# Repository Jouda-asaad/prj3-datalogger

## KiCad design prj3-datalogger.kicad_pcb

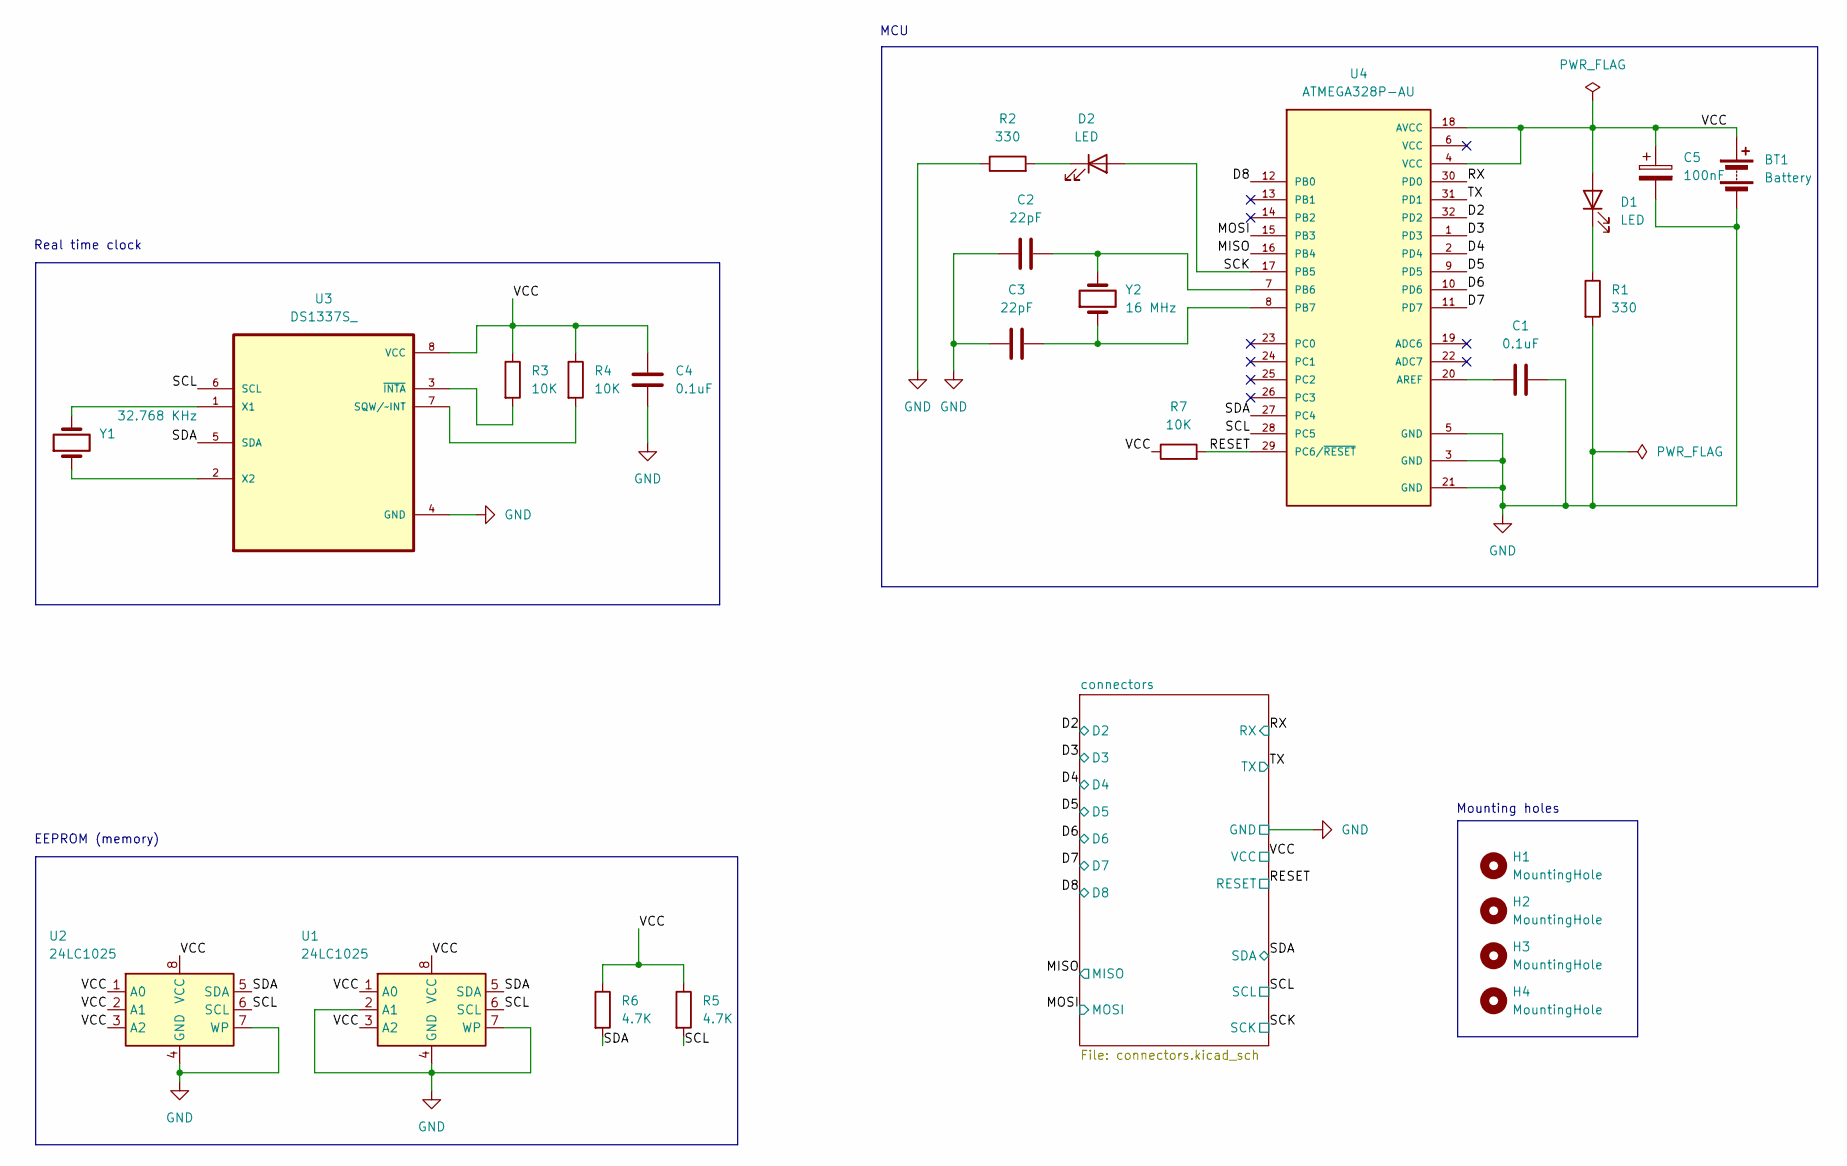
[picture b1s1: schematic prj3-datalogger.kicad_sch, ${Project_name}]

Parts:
BT1: Battery; PinHeader_1x02_P2.54mm_Vertical
C1, C4: 0.1uF; C_0805_2012Metric
C2, C3: 22pF; C_0805_2012Metric
C5: 100nF; C_0805_2012Metric
D1, D2: LED; LED_0805_2012Metric
H1, H2, H3, H4: MountingHole; MountingHole_2.2mm_M2
R1, R2: 330; R_0805_2012Metric
R3, R4, R7: 10K; R_0805_2012Metric
R5, R6: 4.7K; R_0805_2012Metric
U1, U2: 24LC1025; SOIC-8_5.3x5.3mm_P1.27mm
U3: DS1337S_; SOIC127P600X175-8N
U4: ATMEGA328P-AU; QFP80P900X900X120-32N; PARTREV 8271A
Y1: 32.768 KHz; Crystal_SMD_5032-2Pin_5.0x3.2mm_HandSoldering
Y2: 16 MHz; Crystal_SMD_5032-2Pin_5.0x3.2mm_HandSoldering

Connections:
/D2: U4.32 (PD2); also elsewhere on the board
/D3: U4.1 (PD3); also elsewhere on the board
/D4: U4.2 (PD4); also elsewhere on the board
/D5: U4.9 (PD5); also elsewhere on the board
/D6: U4.10 (PD6); also elsewhere on the board
/D7: U4.11 (PD7); also elsewhere on the board
/D8: U4.12 (PB0); also elsewhere on the board
/MISO: U4.16 (PB4); also elsewhere on the board
/MOSI: U4.15 (PB3); also elsewhere on the board
/RESET: R7.2, U4.29 (PC6/~RESET); also elsewhere on the board
/RX: U4.30 (PD0); also elsewhere on the board
/SCK: D2.2 (A), U4.17 (PB5); also elsewhere on the board
/SCL: R5.2, U1.6 (SCL), U2.6 (SCL), U3.6 (SCL), U4.28 (PC5); also elsewhere on the board
/SDA: R6.2, U1.5 (SDA), U2.5 (SDA), U3.5 (SDA), U4.27 (PC4); also elsewhere on the board
/TX: U4.31 (PD1); also elsewhere on the board
/VCC: BT1.1 (+), C4.1, C5.1, D1.2 (A), R3.1, R4.1, R5.1, R6.1, R7.1, U1.1 (A0), U1.3 (A2), U1.8 (VCC), U2.1 (A0), U2.2 (A1), U2.3 (A2), U2.8 (VCC), U3.8 (VCC), U4.4 (VCC), U4.18 (AVCC); also elsewhere on the board
GND: BT1.2 (-), C1.2, C2.1, C3.1, C4.2, C5.2, R1.2, R2.1, U1.2 (A1), U1.4 (GND), U1.7 (WP), U2.4 (GND), U2.7 (WP), U3.4 (GND), U4.3 (GND), U4.5 (GND), U4.21 (GND); also elsewhere on the board
unnamed: D1.1 (K), R1.1
unnamed: D2.1 (K), R2.2
unnamed: R4.2, U3.7 (SQW/~INT)
unnamed: U3.1 (X1), Y1.2
unnamed: U3.2 (X2), Y1.1
unnamed: R3.2, U3.3 (~INTA)
unnamed: C1.1, U4.20 (AREF)
unnamed: C2.2, U4.7 (PB6), Y2.2
unnamed: C3.2, U4.8 (PB7), Y2.1

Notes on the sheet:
EEPROM (memory)
MCU
Mounting holes
Real time clock

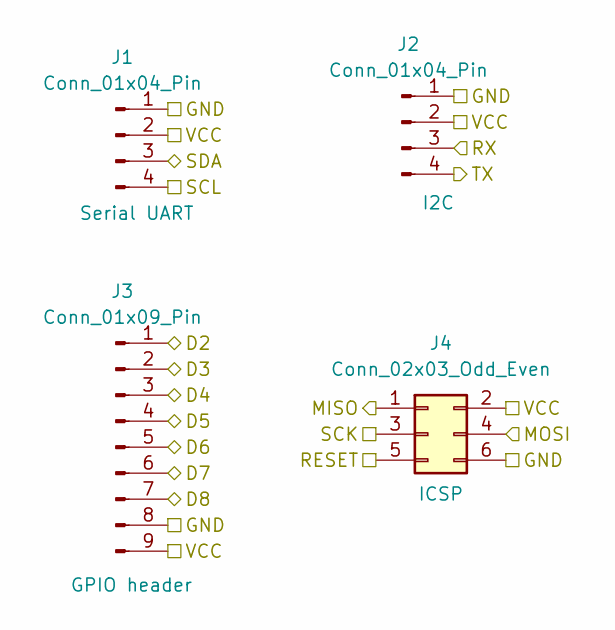
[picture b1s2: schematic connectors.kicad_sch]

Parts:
J1, J2: Conn_01x04_Pin; PinHeader_1x04_P2.54mm_Vertical
J3: Conn_01x09_Pin; PinHeader_1x10_P2.54mm_Vertical
J4: Conn_02x03_Odd_Even; PinHeader_2x03_P2.54mm_Vertical

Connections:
/D2: J3.1; also elsewhere on the board
/D3: J3.2; also elsewhere on the board
/D4: J3.3; also elsewhere on the board
/D5: J3.4; also elsewhere on the board
/D6: J3.5; also elsewhere on the board
/D7: J3.6; also elsewhere on the board
/D8: J3.7; also elsewhere on the board
/MISO: J4.1; also elsewhere on the board
/MOSI: J4.4; also elsewhere on the board
/RESET: J4.5; also elsewhere on the board
/RX: J2.3; also elsewhere on the board
/SCK: J4.3; also elsewhere on the board
/SCL: J1.4; also elsewhere on the board
/SDA: J1.3; also elsewhere on the board
/TX: J2.4; also elsewhere on the board
/VCC: J1.2, J2.2, J3.9, J4.2; also elsewhere on the board
GND: J1.1, J2.1, J3.8, J4.6; also elsewhere on the board

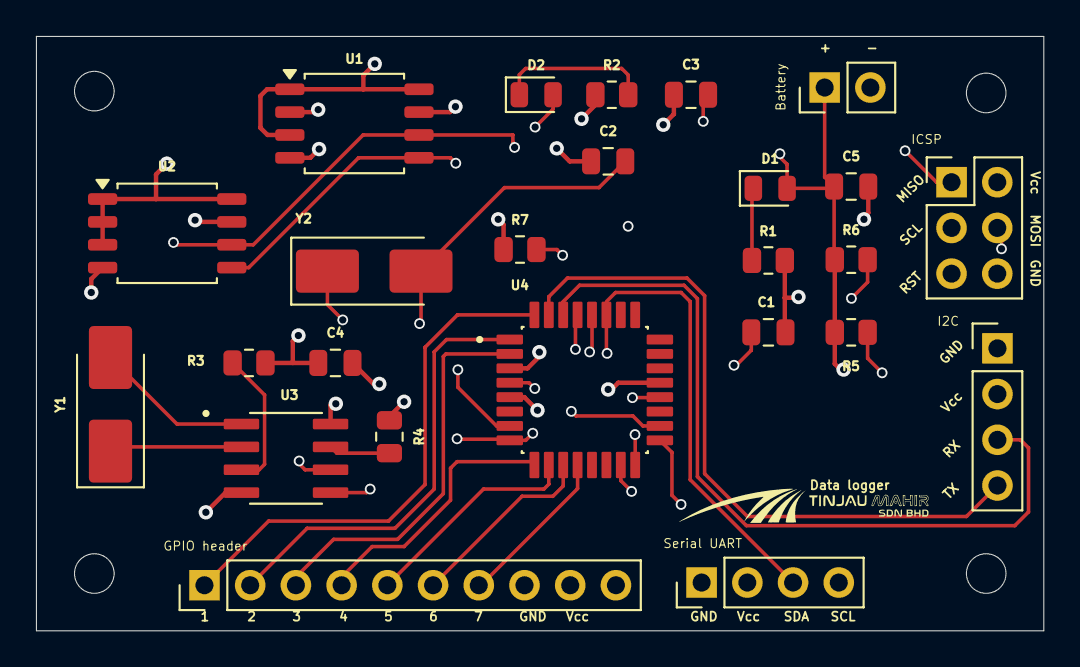
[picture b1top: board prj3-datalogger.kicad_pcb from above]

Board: 4 copper layers, 56.0 x 33.0 mm, 29 parts (0 on the bottom side), 26 nets.
